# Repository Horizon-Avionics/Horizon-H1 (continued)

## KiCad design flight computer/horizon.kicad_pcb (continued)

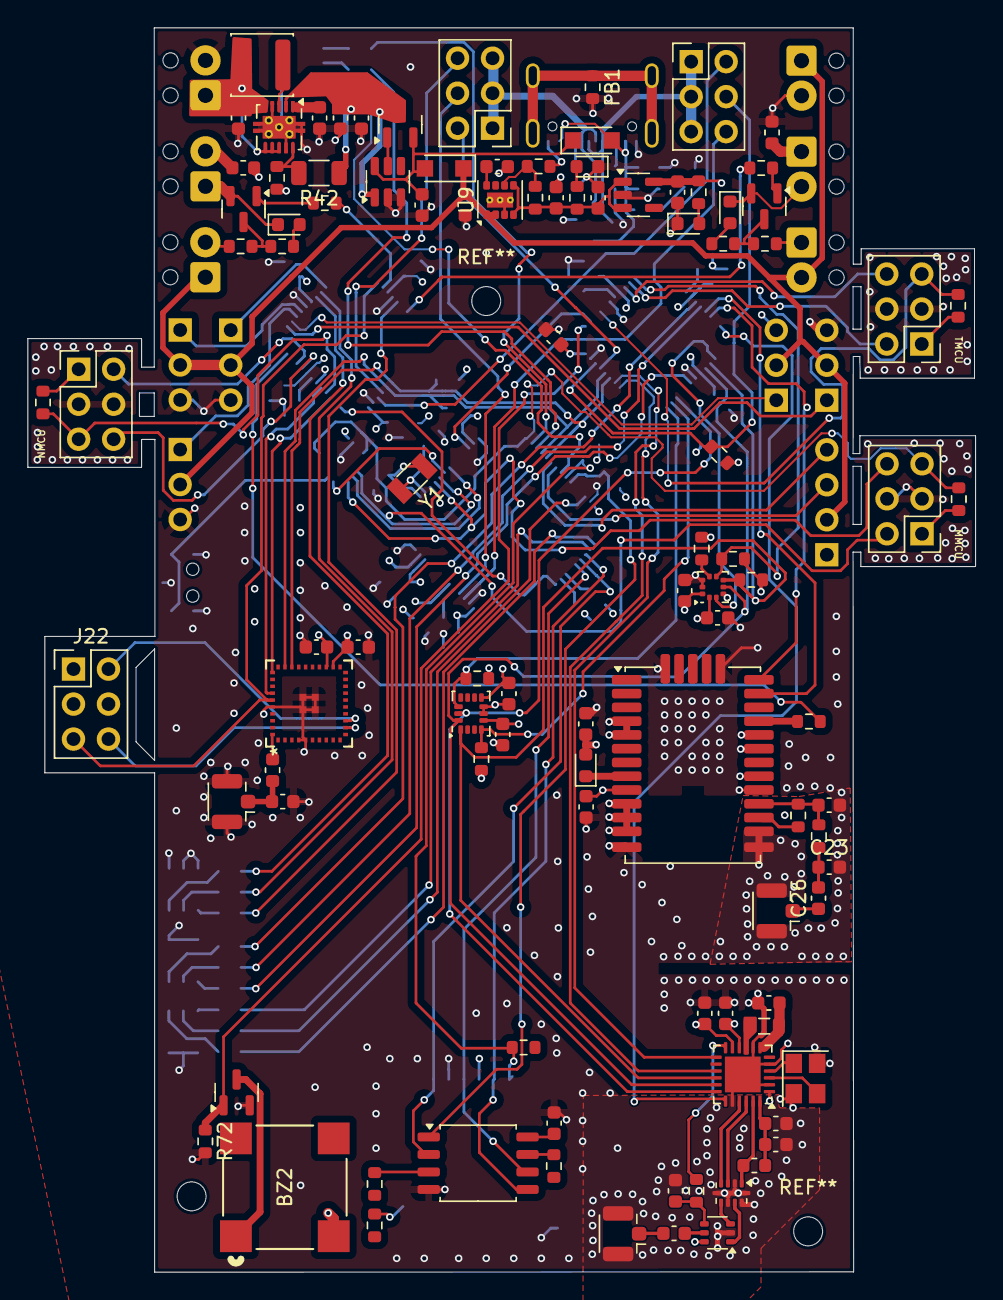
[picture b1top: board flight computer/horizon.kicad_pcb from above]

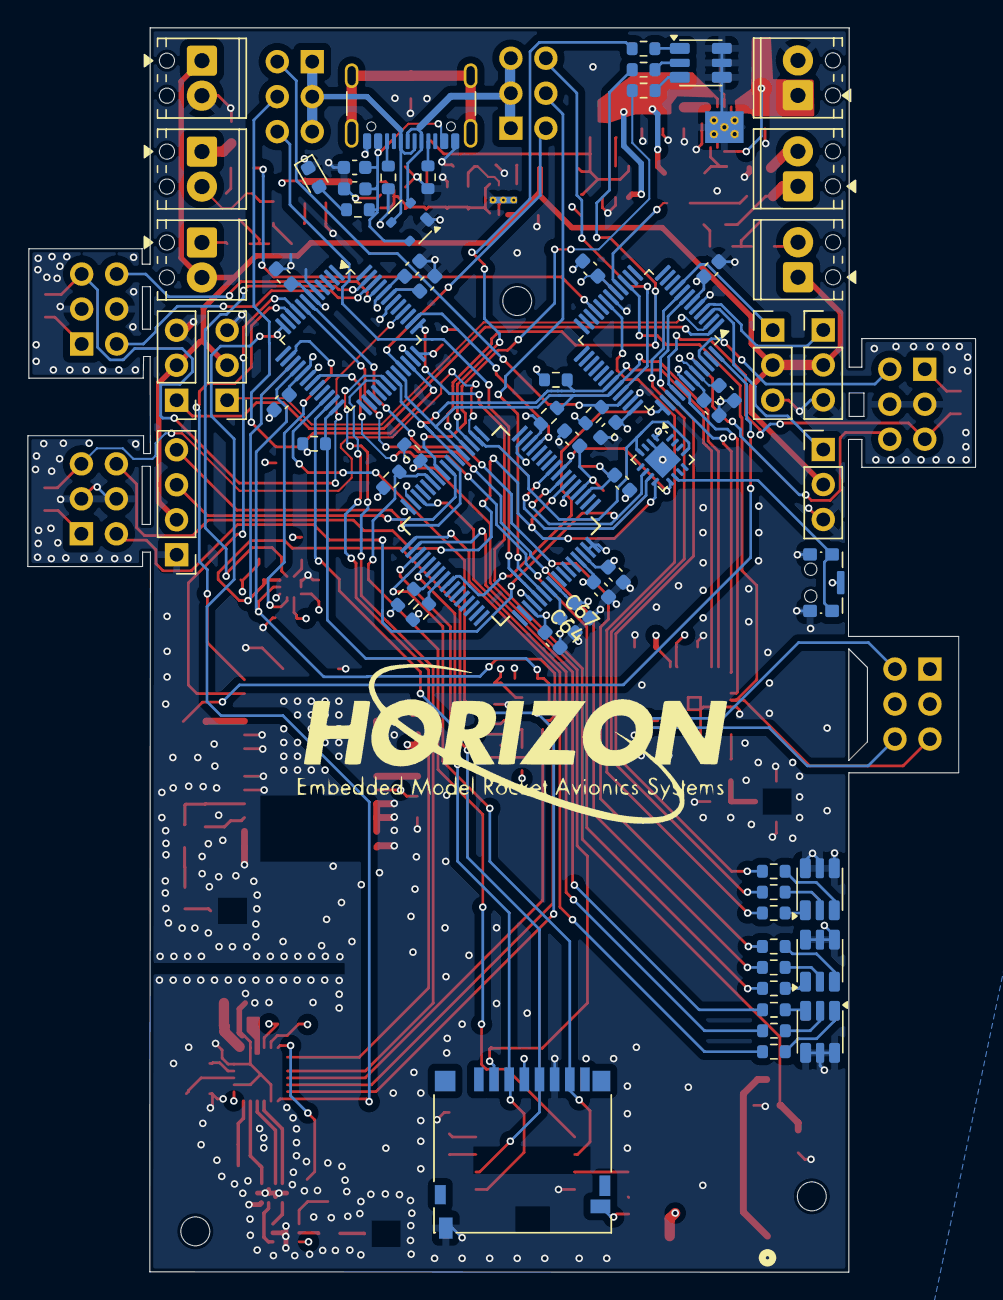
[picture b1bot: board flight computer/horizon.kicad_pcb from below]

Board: 4 copper layers, 68.8 x 90.3 mm, 169 parts (66 on the bottom side), 147 nets.

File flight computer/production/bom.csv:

Designator,Footprint,Quantity,Value,LCSC Part #
1X3SERVO1,PinHeader_1x03_P2.54mm_Vertical,1,Conn_01x03,
BZ2,MLT-8530_JHE,1,Buzzer,
"C1, C2",0603,2,100 nF,
"C10, C17",0603,2,12pF,
"C11, C13, C15, C19, C44, C45, C5, C50, C51, C6, C7, C77, C8, C9",0603,14,100nF,
"C12, C22, C35, C63, C72",0603,5,1uF,
C16,0603,1,4n7,
"C18, C67",0603,2,4.7uF,
"C20, C23, R1",0603,3,DNP,
"C21, C24, C25, C28, C32",0603,5,10uF,
C26,0603,1,100pF,
C27,0603,1,100n,
C33,0603,1,3.3 nF,
C34,0603,1,22uF,
C36,0603,1,1u,
"C37, C38",0603,2,100nF,C14663
C4,0603,1,1.2 pF,
C40,0603,1,470nF,C1623
C46,0603,1,1nF,C100040
C47,0603,1,47nF,C107093
C48,0603,1,47pF,C105622
C49,0603,1,100pF,C14665
"C64, C65, C66",0603,3,0.1uF,
D1,0603,1,D_Schottky,
"D15, D16, D17, D18",LED_ROHM_SMLVN6,4,SMLVN6RGB,
"D20, D26",Nexperia_CFP3_SOD-123W,2,PMEG6020ER,
"D21, D22, D3, D4, D7",0603,5,LED,
D8,SOT-143,1,PRTR5V0U2X,
"F1, F2",0603,2,Polyfuse,
FB1,0603,1,BLM18AG601SN1D,
J1,microSD_HC_Hirose_DM3D-SF,1,Micro_SD_Card_Det1,
J10,"TerminalBlock_Phoenix_MPT-0,5-2-2.54_1x02_P2.54mm_Horizontal",1,Conn_01x02_Pin,
J11,USB_C_Receptacle_GCT_USB4105-xx-A_16P_TopMnt_Horizontal,1,USB_C_Receptacle_USB2.0_16P,
J12,PinHeader_1x04_P2.54mm_Vertical,1,Conn_01x04,
"J13, J14, J6, J9",PinHeader_1x03_P2.54mm_Vertical,4,1x3 servo,
"J15, J16","TerminalBlock_Phoenix_MPT-0,5-2-2.54_1x02_P2.54mm_Horizontal",2,arming terminal,
"J17, J3, J4",U.FL_Hirose_U.FL-R-SMT-1_Vertical,3,H9161TR-ND,
"J18, J2, J21, J7, J8",PinHeader_2x03_P2.54mm_Vertical,5,Conn_02x03_Counter_Clockwise,
"J19, J20","TerminalBlock_Phoenix_MPT-0,5-2-2.54_1x02_P2.54mm_Horizontal",2,Screw_Terminal_01x02,
J22,PinHeader_2x03_P2.54mm_Vertical,1,Bluetooth Programming,
J5,"TerminalBlock_Phoenix_MPT-0,5-2-2.54_1x02_P2.54mm_Horizontal",1,Screw_Term,
L10,0603,1,47nH,C285885
L11,0805,1,15uH,C383402
L2,L_APV_ANR4018,1,2.2uH,
L3,0603,1,3.9 nH,
Q2,SOT-23,1,DMG2301L,
Q7,SOT-23,1,BSS138,
"Q8, Q9",SOT-23,2,IRLML6402,
"R10, R13, R26, R29, R30",0603,5,2.2k,
"R11, R12, R54, R55",0603,4,10kΩ,
"R14, R9",0603,2,1.5k,
R2,0603,1,0R,
"R20, R21",0603,2,5k1,
"R22, R47",0603,2,330,
"R27, R3, R38, R39, R4, R5, R52, R53, R56, R78, R80",0603,11,10k,
R42,1206,1,900k,
"R43, R45",0603,2,100k,
R44,0603,1,350k,
"R46, R79, R81",0603,3,100,
"R58, R59",0603,2,1k,
"R6, R7",0603,2,4.7k,
R72,0603,1,2k2,
R8,0603,1,100,C105588
"R87, R88, R89, R90, R91, R92, R93, R94, R95, R96, R97, R98",0603,12,220,
SAMD21G18A-AU1,TQFP-48_7x7mm_P0.5mm,1,NMCU,
SAMD21G18A-AU2,TQFP-48_7x7mm_P0.5mm,1,TMCU,
SW1,SW_SPST_CK_KMS2xxGP,1,CK_KMS2xxG,
U1,QFP50P1200X1200X160-64N,1,MMCU,
U10,LGA-14_3x2.5mm_P0.5mm_LayoutBorder3x4y,1,LSM6DS3,
U11,BGM220S_SIL,1,BGM220SC12WGA2R,
U13,TSOT-23-6,1,LTC4412xS6,
U15,SOT-23-5,1,AP2112K-3.3,
U16,QFN-24-1EP_4x4mm_P0.5mm_EP2.6x2.6mm,1,SX1262IMLTRT,C191341
U17,SOT-363_SC-70-6,1,PE4259, C470892
U2,QFN-16-1EP_3x3mm_P0.5mm_EP1.9x1.9mm,1,MKL02Z32VFG4,
U3,Texas_S-PVSON-N10_ThermalVias,1,TPS61200DRC,
U5,ST_HLGA-10_2x2mm_P0.5mm_LayoutBorder3x2y,1,LPS22HB,
U6,Quectel_L96,1,GPS,
U8,SOIC-8_5.3x5.3mm_P1.27mm,1,NAND,
U9,Texas_SIL0008D_MicroSiP-8-1EP_2.8x3mm_P0.65mm_EP1.1x1.9mm_ThermalVias,1,TPS82130,
Y1,Crystal_SMD_3215-2Pin_3.2x1.5mm,1,32 kHZ,
Y2,Crystal_SMD_3225-4Pin_3.2x2.5mm,1,32MHz,C37635386

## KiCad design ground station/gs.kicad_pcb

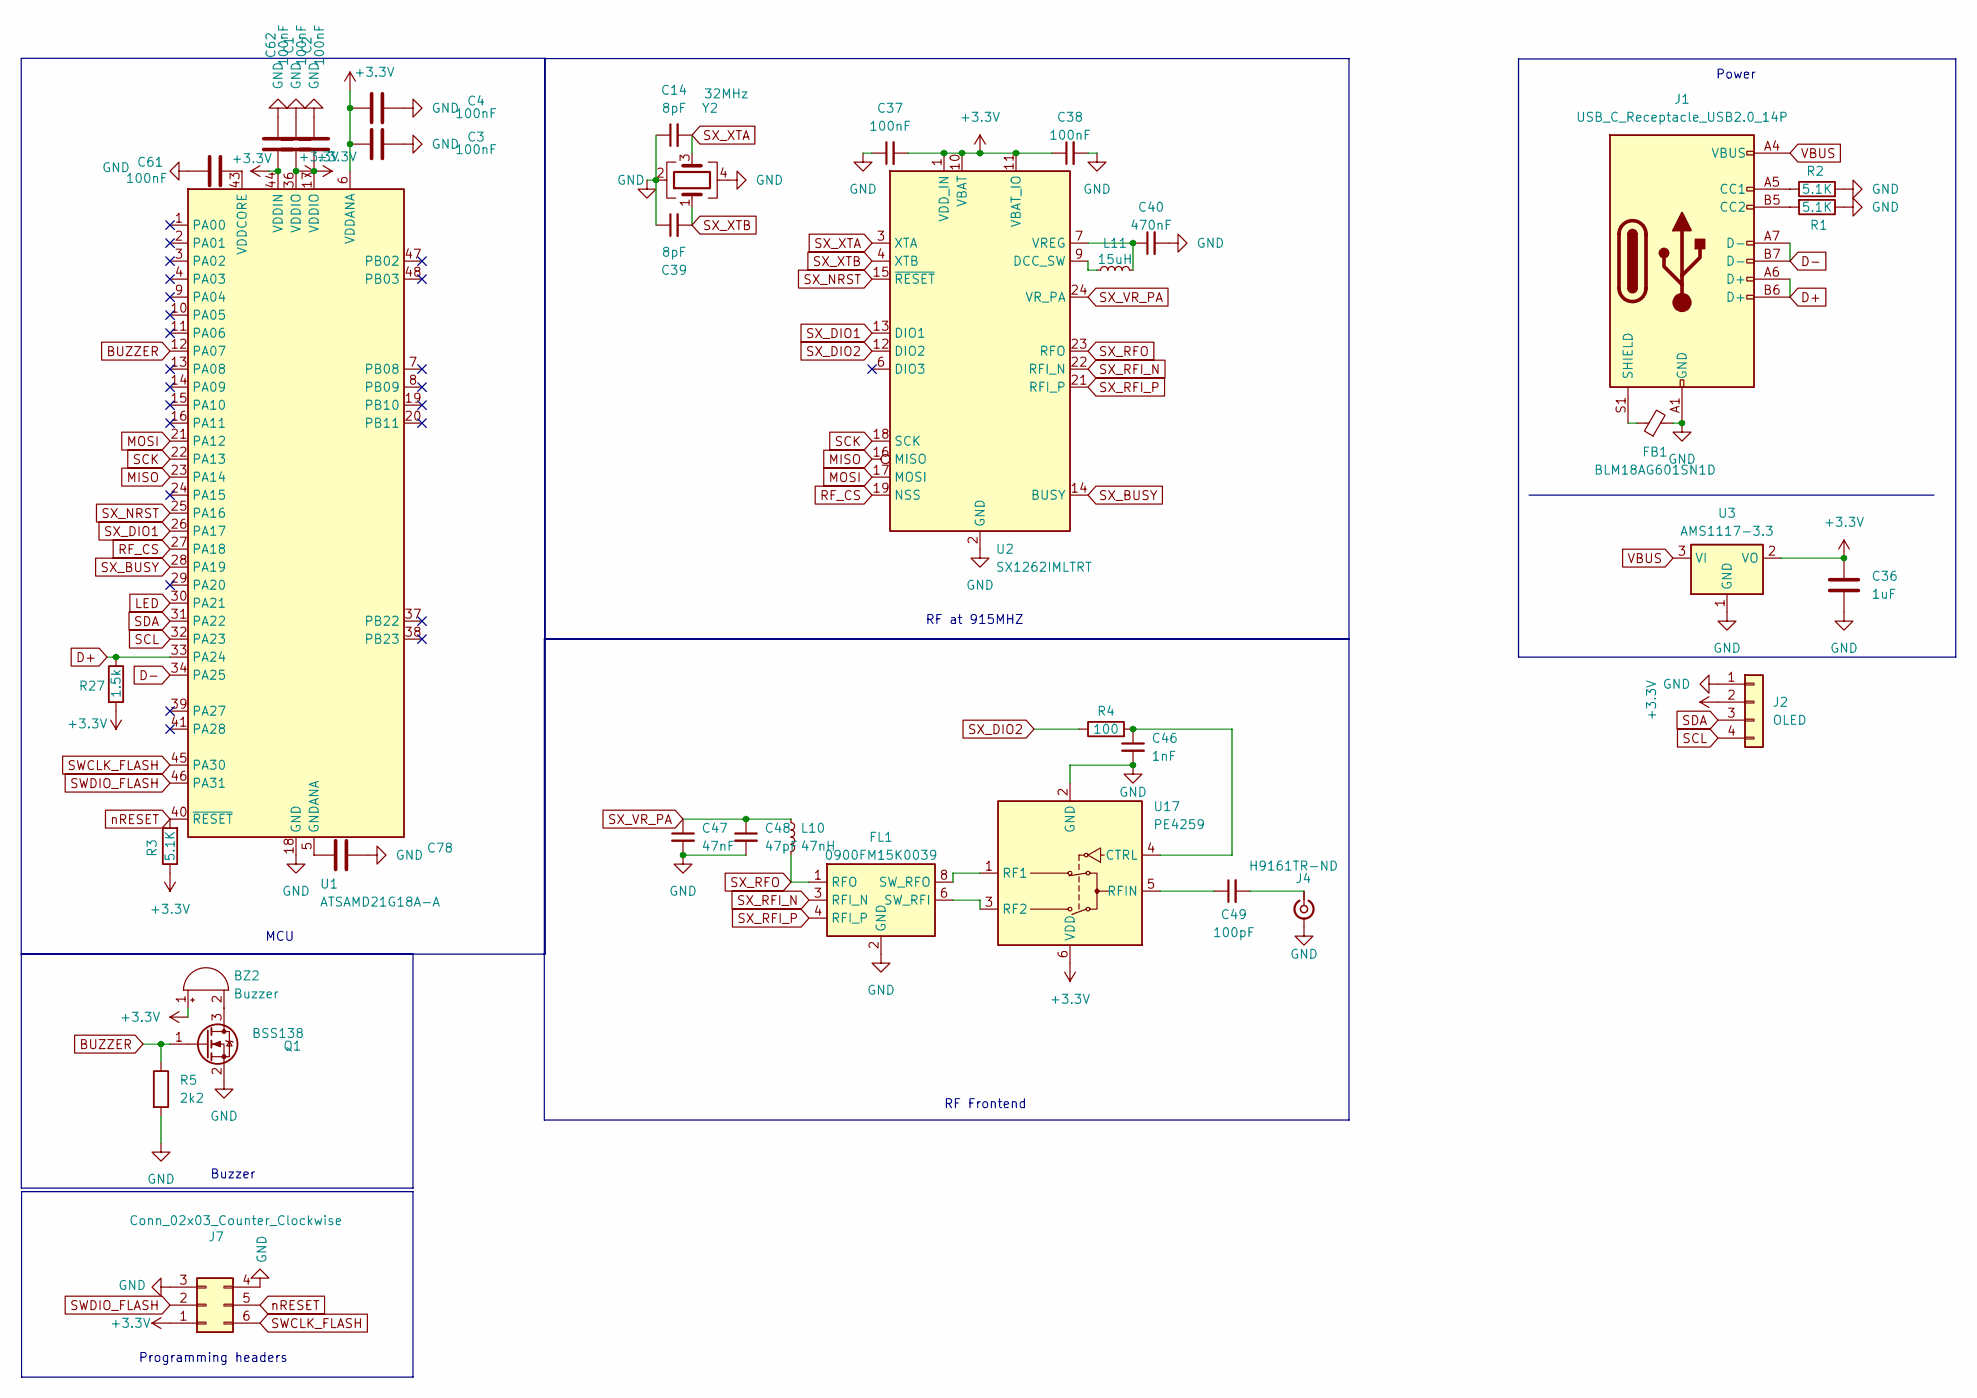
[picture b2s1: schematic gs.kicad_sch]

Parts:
BZ2: Buzzer; MagneticBuzzer_PUI_AT-0927-TT-6-R
C1, C2, C3, C4, C61, C62, C78: 100nF; C_0603_1608Metric
C14, C39: 8pF; C_0603_1608Metric; LCSC Part C327316
C36: 1uF; C_0603_1608Metric
C37, C38: 100nF; C_0603_1608Metric; LCSC Part C14663
C40: 470nF; C_0603_1608Metric; LCSC Part C1623
C46: 1nF; C_0603_1608Metric; LCSC Part C100040
C47: 47nF; C_0603_1608Metric; LCSC Part C107093
C48: 47pF; C_0603_1608Metric; LCSC Part C105622
C49: 100pF; C_0603_1608Metric; LCSC Part C14665
FB1: BLM18AG601SN1D; R_0603_1608Metric; LCSC Part C19330
FL1: 0900FM15K0039; Balun_Johanson_0900FM15K0039; LCSC Part C5224443
J1: USB_C_Receptacle_USB2.0_14P; USB_C_Receptacle_HCTL_HC-TYPE-C-16P-01A
J2: OLED; NS-Tech_Grove_1x04_P2mm_Vertical
J4: H9161TR-ND; U.FL_Hirose_U.FL-R-SMT-1_Vertical
J7: Conn_02x03_Counter_Clockwise; PinHeader_2x03_P2.54mm_Vertical
L10: 47nH; L_0603_1608Metric; LCSC Part C285885
L11: 15uH; L_0805_2012Metric; LCSC Part C383402
Q1: BSS138; SOT-23
R1, R2, R3: 5.1K; C_0603_1608Metric
R4: 100; R_0603_1608Metric
R5: 2k2; R_0603_1608Metric
R27: 1.5k; R_0603_1608Metric
U1: ATSAMD21G18A-A; TQFP-48_7x7mm_P0.5mm
U2: SX1262IMLTRT; QFN-24-1EP_4x4mm_P0.5mm_EP2.6x2.6mm
U3: AMS1117-3.3; SOT-223-3_TabPin2
U17: PE4259; SOT-363_SC-70-6; LCSC Part C470892
Y2: 32MHz; Crystal_SMD_3225-4Pin_3.2x2.5mm; LCSC Part C37635386

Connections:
+3.3V: BZ2.1 (+), C1.2, C2.2, C3.2, C4.2, C36.1, C37.2, C38.1, C62.2, J2.2, J7.1, R3.1, R27.2, U1.6 (VDDANA), U1.17 (VDDIO), U1.36 (VDDIO), U1.44 (VDDIN), U2.1 (VDD_IN), U2.10 (VBAT), U2.11 (VBAT_IO), U3.2 (VO), U17.6 (VDD)
BUZZER: Q1.1 (G), R5.1, U1.12 (PA07)
D+: J1.A6 (D+), J1.B6 (D+), R27.1, U1.33 (PA24)
D-: J1.A7 (D-), J1.B7 (D-), U1.34 (PA25)
GND: C1.1, C2.1, C3.1, C4.1, C14.1, C36.2, C37.1, C38.2, C39.1, C40.2, C46.2, C47.2, C48.2, C61.1, C62.1, C78.1, FB1.2, FL1.2 (GND), FL1.5 (GND), FL1.7 (GND), FL1.9 (GND), FL1.10 (GND), J1.A1 (GND), J1.A12 (GND), J1.B1 (GND), J1.B12 (GND), J2.1, J4.2 (Ext), J7.3, J7.4, Q1.2 (S), R1.1, R2.2, R5.2, U1.18 (GND), U1.35 (GND), U1.42 (GND), U2.2 (GND), U2.5 (GND), U2.8 (GND), U2.20 (GND), U2.25 (GND), U3.1 (GND), U17.2 (GND), Y2.2, Y2.4
LED: U1.30 (PA21)
MISO: U1.23 (PA14), U2.16 (MISO)
MOSI: U1.21 (PA12), U2.17 (MOSI)
unnamed: BZ2.2 (-), Q1.3 (D)
unnamed: FL1.6 (SW_RFI), U17.3 (RF2)
unnamed: FL1.8 (SW_RFO), U17.1 (RF1)
unnamed: J1.A5 (CC1), R2.1
unnamed: J1.B5 (CC2), R1.2
unnamed: FB1.1, J1.S1 (SHIELD)
unnamed: C49.2, J4.1 (In)
unnamed: C78.2, U1.5 (GNDANA)
unnamed: C61.2, U1.43 (VDDCORE)
unnamed: L11.1, U2.9 (DCC_SW)
unnamed: C40.1, L11.2, U2.7 (VREG)
unnamed: C46.1, R4.2, U17.4 (CTRL)
unnamed: C49.1, U17.5 (RFIN)
RF_CS: U1.27 (PA18), U2.19 (NSS)
SCK: U1.22 (PA13), U2.18 (SCK)
SCL: J2.4, U1.32 (PA23)
SDA: J2.3, U1.31 (PA22)
SWCLK_FLASH: J7.6, U1.45 (PA30)
SWDIO_FLASH: J7.2, U1.46 (PA31)
SX_BUSY: U1.28 (PA19), U2.14 (BUSY)
SX_DIO1: U1.26 (PA17), U2.13 (DIO1)
SX_DIO2: R4.1, U2.12 (DIO2)
SX_NRST: U1.25 (PA16), U2.15 (~RESET)
SX_RFI_N: FL1.3 (RFI_N), U2.22 (RFI_N)
SX_RFI_P: FL1.4 (RFI_P), U2.21 (RFI_P)
SX_RFO: FL1.1 (RFO), L10.2, U2.23 (RFO)
SX_VR_PA: C47.1, C48.1, L10.1, U2.24 (VR_PA)
SX_XTA: C14.2, U2.3 (XTA), Y2.3
SX_XTB: C39.2, U2.4 (XTB), Y2.1
VBUS: J1.A4 (VBUS), J1.A9 (VBUS), J1.B4 (VBUS), J1.B9 (VBUS), U3.3 (VI)
nRESET: J7.5, R3.2, U1.40 (~RESET)

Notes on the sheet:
Programming headers
Buzzer
RF at 915MHZ
RF Frontend
Power
MCU

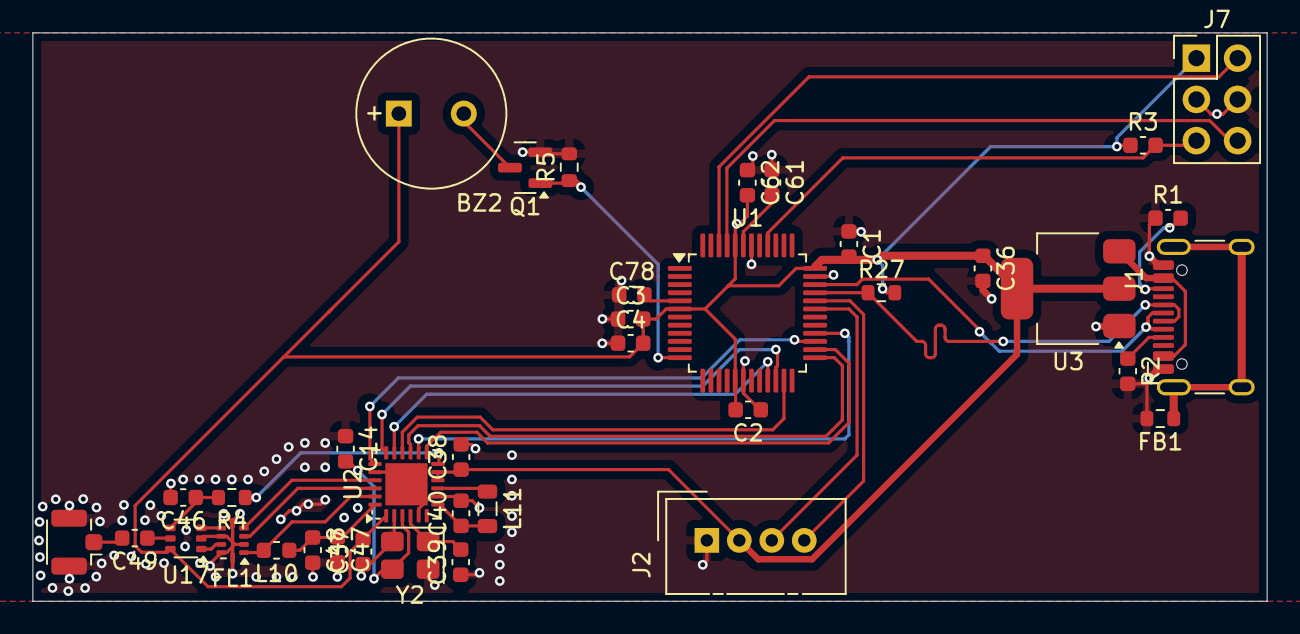
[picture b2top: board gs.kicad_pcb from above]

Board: 2 copper layers, 76.0 x 35.0 mm, 38 parts (0 on the bottom side), 38 nets.

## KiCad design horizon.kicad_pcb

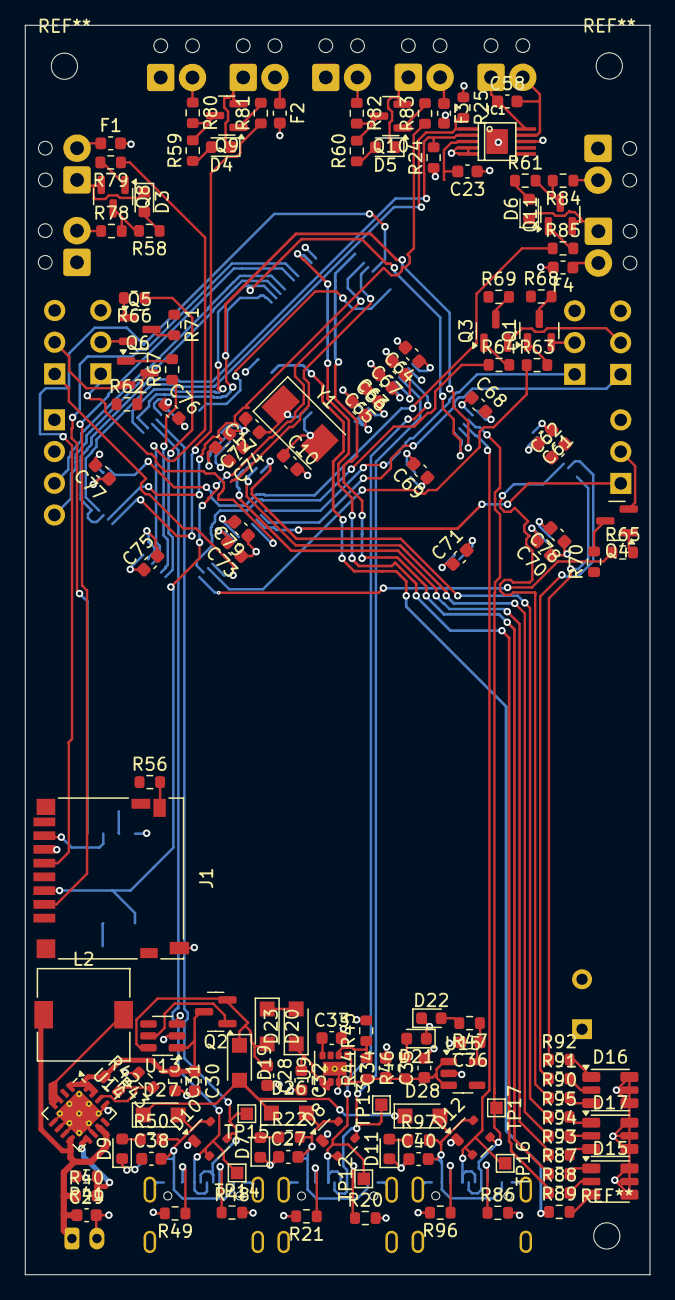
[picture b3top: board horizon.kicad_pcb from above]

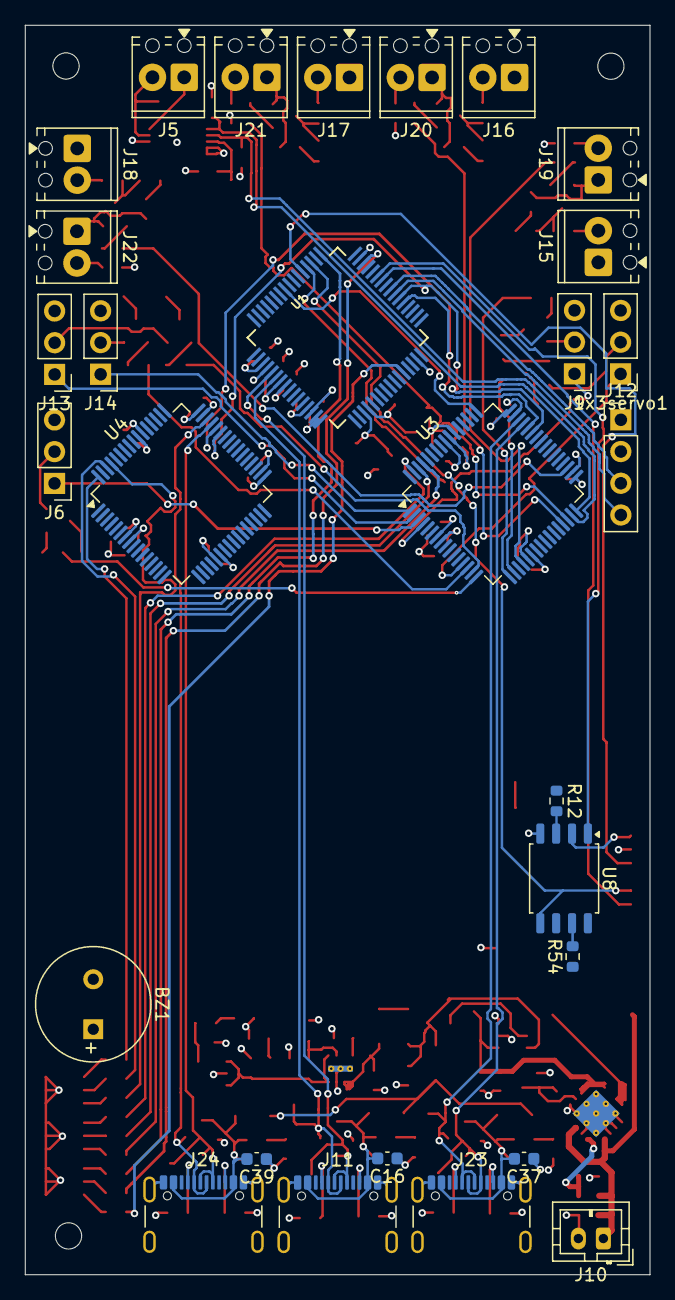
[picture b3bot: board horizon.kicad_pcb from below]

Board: 4 copper layers, 50.0 x 100.0 mm, 164 parts (29 on the bottom side), 131 nets.

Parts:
1x3servo1: Conn_01x03; PinHeader_1x03_P2.54mm_Vertical
BZ1: Buzzer; MagneticBuzzer_PUI_AT-0927-TT-6-R
C10, C17: 12pF; C_0603_1608Metric
C16, C37, C39: 4n7; C_0603_1608Metric
C23: 100 nF; C_0603_1608Metric
C27, C38, C40: 100n; C_0603_1608Metric
C28, C32: 10uF; C_0603_1608Metric
C29: 10u; C_0603_1608Metric
C30: 2u2; C_0603_1608Metric
C31: 100u; C_0603_1608Metric
C33: 3.3 nF; C_0603_1608Metric
C34: 22uF; C_0603_1608Metric
C35, C63, C72: 1uF; C_0603_1608Metric
C36: 1u; C_0603_1608Metric
C58, C61, C62, C68, C69, C70, C71, C73, C74, C75, C76, C77, C78, C79: 100nF; C_0603_1608Metric
C64, C65, C66: 0.1uF; C_0603_1608Metric
C67: 4.7uF; C_0603_1608Metric
D3, D4, D5, D6, D7, D9, D11, D21, D22: LED; LED_0603_1608Metric
D8, D10, D12: PRTR5V0U2X; SOT-143
D15, D16, D17: SMLVN6RGB; LED_ROHM_SMLVN6
D19, D20, D23, D26, D27, D28: PMEG6020ER; Nexperia_CFP3_SOD-123W
F1, F2, F3, F4: Polyfuse; Fuse_0603_1608Metric
IC1: A3909; MSOP10-PAD
J1: Micro_SD_Card_Det1; microSD_HC_Hirose_DM3D-SF
J5: Screw_Term; TerminalBlock_Phoenix_MPT-0,5-2-2.54_1x02_P2.54mm_Horizontal
J6, J9, J13, J14: 1x3 servo; PinHeader_1x03_P2.54mm_Vertical
J10: Conn_01x02_Pin; JST_PH_B2B-PH-K_1x02_P2.00mm_Vertical
J11, J23, J24: USB_C_Receptacle_USB2.0_16P; USB_C_Receptacle_GCT_USB4105-xx-A_16P_TopMnt_Horizontal
J12: Conn_01x04; PinHeader_1x04_P2.54mm_Vertical
J15, J16, J17, J18: arming terminal; TerminalBlock_Phoenix_MPT-0,5-2-2.54_1x02_P2.54mm_Horizontal
J19, J20, J21, J22: Screw_Terminal_01x02; TerminalBlock_Phoenix_MPT-0,5-2-2.54_1x02_P2.54mm_Horizontal
L2: SLF7055T-6R8N2R8-3PF; L_7.3x7.3_H4.5
Q1, Q3, Q4, Q5, Q6, Q8, Q9, Q10, Q11: IRLML6402; SOT-23
Q2: DMG2301L; SOT-23
R12, R54: 10kΩ; R_0603_1608Metric
R20, R21, R48, R49, R86, R96: 5k1; R_0603_1608Metric
R22, R47, R50, R97: 330; R_0603_1608Metric
R24, R25, R56, R78, R80, R82, R84: 10k; R_0603_1608Metric
R40, R41, R43, R45, R62, R68, R69, R70, R71: 100k; R_0603_1608Metric
R42: 430k; R_0603_1608Metric
R44: 350k; R_0603_1608Metric
R46, R63, R64, R65, R66, R67, R79, R81, R83, R85: 100; R_0603_1608Metric
R58, R59, R60, R61: 1k; R_0603_1608Metric
R87, R88, R89, R90, R91, R92, R93, R94, R95: 220; R_0603_1608Metric
TP12, TP13, TP14, TP15, TP16, TP17: TestPoint; TestPoint_Pad_1.0x1.0mm
U1: MMCU; QFP50P1200X1200X160-64N
U3: NMCU; TQFP-64_10x10mm_P0.5mm
U4: TMCU; TQFP-64_10x10mm_P0.5mm
U8: NAND; SOIC-8_5.3x5.3mm_P1.27mm
U9: TPS82130; Texas_SIL0008D_MicroSiP-8-1EP_2.8x3mm_P0.65mm_EP1.1x1.9mm_T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
U13: LTC4412xS6; TSOT-23-6
U14: TPS61092; Texas_RSA_VQFN-16-1EP_4x4mm_P0.65mm_EP2.7x2.7mm_ThermalVias
U15: AP2112K-3.3; SOT-23-5
Y1: Crystal; Crystal_SMD_0603-2Pin_6.0x3.5mm

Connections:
1B: R87.1, U1.49 (D10/TX2/PWM)
1G: R88.1, U1.46 (D9/RX2/PWM)
1R: R89.1, U1.28 (D3/CAN-TX/PWM)
2B: R92.1, U4.64 (PB03)
2G: R91.1, U4.62 (PB01)
2R: R90.1, U4.61 (PB00)
3B: R95.1, U3.63 (PB02)
3G: R94.1, U3.62 (PB01)
3R: R93.1, U3.61 (PB00)
+3.3V: BZ1.1 (+), C36.1, C62.2, C63.1, C64.1, C65.1, C66.1, C68.2, C69.2, C70.2, C71.2, C73.2, C74.2, C75.2, C76.2, C77.2, J1.4 (VDD), R12.1, R47.1, R54.1, R56.1, U1.3 (VCC), U1.8 (VREGIN), U1.13 (VCCA), U1.14 (VREF-H), U1.21 (VBAT), U1.30 (VCC), U1.48 (VCC), U3.8 (VDDANA), U3.21 (VDDIO), U3.34 (VDDIO), U3.48 (VDDIO), U3.56 (VDDIN), U4.8 (VDDANA), U4.21 (VDDIO), U4.34 (VDDIO), U4.48 (VDDIO), U4.56 (VDDIN), U8.8 (VCC), U15.5 (VOUT)
+5V: C23.2, D20.1 (K), D23.2 (A), IC1.3 (VBB), J12.2, J15.1, J16.1, J17.1, J18.1, R62.1, R68.1, R69.1, R70.1, R71.1
CAM_RX: J12.3, U1.40 (D1/TX1/TOUCH)
CAM_TX: J12.4, U1.39 (D0/RX1/TOUCH)
CS_NAND MMCU: U1.43 (D15/A1/TOUCH), U8.1 (~CS)
CS_SD MMCU: J1.2 (DAT3/CD), U1.42 (D25/PWM/TOUCH)
D+ DMCU-1: D10.2 (I/O1), J23.A6 (D+), J23.B6 (D+), TP14.1, U3.45 (PA24)
D+ DMCU-2: D12.2 (I/O1), J24.A6 (D+), J24.B6 (D+), TP16.1, U4.45 (PA24)
D+ MMCU: D8.2 (I/O1), J11.A6 (D+), J11.B6 (D+), TP12.1, U1.5 (USB-P)
D- DMCU-1: D10.3 (I/O2), J23.A7 (D-), J23.B7 (D-), TP15.1, U3.46 (PA25)
D- DMCU-2: D12.3 (I/O2), J24.A7 (D-), J24.B7 (D-), TP17.1, U4.46 (PA25)
D- MMCU: D8.3 (I/O2), J11.A7 (D-), J11.B7 (D-), TP13.1, U1.6 (USB-M)
DIR1: IC1.2 (IN2), R24.2, U3.31 (PA14)
GND: 1x3servo1.3, C10.2, C16.1, C17.2, C23.1, C27.1, C28.2, C29.2, C30.2, C31.2, C32.2, C33.2, C34.2, C35.2, C36.2, C37.1, C38.1, C39.1, C40.1, C61.1, C62.1, C63.2, C64.2, C65.2, C66.2, C67.2, C68.1, C69.1, C70.1, C71.1, C72.1, C73.1, C74.1, C75.1, C76.1, C77.1, C78.1, C79.1, D7.1 (K), D8.1 (GND), D9.1 (K), D10.1 (GND), D11.1 (K), D12.1 (GND), D15.4 (GK), D15.5 (RK), D15.6 (BK), D16.4 (GK), D16.5 (RK), D16.6 (BK), D17.4 (GK), D17.5 (RK), D17.6 (BK), D21.1 (K), D22.1 (K), F1.2, F2.2, F3.2, F4.2, IC1.4 (IN3), IC1.5 (IN4), IC1.8 (GND), IC1.TP (GND), J1.6 (VSS), J1.10 (SHIELD), J6.3, J9.3, J10.2, J11.A1 (GND), J11.A12 (GND), J11.B1 (GND), J11.B12 (GND), J11.S1 (SHIELD), J12.1, J13.3, J14.3, J23.A1 (GND), J23.A12 (GND), J23.B1 (GND), J23.B12 (GND), J23.S1 (SHIELD), J24.A1 (GND), J24.A12 (GND), J24.B1 (GND), J24.B12 (GND), J24.S1 (SHIELD), R20.2, R21.2, R24.1, R25.1, R41.2, R43.2, R45.2, R48.2, R49.2, R86.2, R96.2, U1.4 (VSS), U1.15 (VREF-L), U1.16 (VSSA), U1.31 (VSS), U1.47 (VSS), U3.22 (GND), U3.33 (GND), U3.47 (GND), U3.54 (GND), U4.22 (GND), U4.33 (GND), U4.47 (GND), U4.54 (GND), U8.4 (GND), U9.3 (GND), U9.9 (GND), U13.2 (GND), U13.3 (CTL), U14.5 (PGND), U14.6 (PGND), U14.7 (PGND), U14.10 (SYNC), U14.13 (GND), U14.17 (PAD), U15.2 (GND)
I2C0_SCL: U1.37 (D19/A5/SCL0/TOUCH), U3.44 (PA23), U4.44 (PA23)
I2C0_SDA: U1.38 (D18/A4/SDA0/TOUCH), U3.43 (PA22), U4.43 (PA22)
NAND_MISO MMCU: J1.7 (DAT0), U1.52 (D12/MISO), U8.2 (DO/IO_{1})
NAND_MOSI MMCU: J1.3 (CMD), U1.51 (D11/MOSI), U8.5 (DI/IO_{0})
unnamed: 1x3servo1.2, Q6.2 (S)
unnamed: D3.2 (A), R58.1
unnamed: D3.1 (K), J19.1, Q8.2 (S)
unnamed: D4.2 (A), R59.1
unnamed: D4.1 (K), J20.1, Q9.2 (S)
unnamed: D5.2 (A), R60.1
unnamed: D5.1 (K), J21.1, Q10.2 (S)
unnamed: D6.2 (A), R61.1
unnamed: D6.1 (K), J22.1, Q11.2 (S)
unnamed: D7.2 (A), R22.1
unnamed: D9.2 (A), R50.1
unnamed: C37.2, C38.2, D10.4 (VCC), D27.2 (A), J23.A4 (VBUS), J23.A9 (VBUS), J23.B4 (VBUS), J23.B9 (VBUS), R50.2
unnamed: D11.2 (A), R97.1
unnamed: C39.2, C40.2, D12.4 (VCC), D28.2 (A), J24.A4 (VBUS), J24.A9 (VBUS), J24.B4 (VBUS), J24.B9 (VBUS), R97.2
unnamed: D15.1 (BA), R87.2
unnamed: D15.3 (GA), R89.2
unnamed: D15.2 (RA), R88.2
unnamed: D16.1 (BA), R92.2
unnamed: D16.3 (GA), R90.2
unnamed: D16.2 (RA), R91.2
unnamed: D17.1 (BA), R95.2
unnamed: D17.3 (GA), R93.2
unnamed: D17.2 (RA), R94.2
unnamed: D21.2 (A), R46.2
unnamed: D22.2 (A), R47.2
unnamed: C32.1, D23.1 (K), U9.1 (EN), U9.2 (VIN)
unnamed: C16.2, C27.2, D8.4 (VCC), D26.2 (A), J11.A4 (VBUS), J11.A9 (VBUS), J11.B4 (VBUS), J11.B9 (VBUS), R22.2
unnamed: C58.1, IC1.10 (OUT1), J5.1
unnamed: C58.2, IC1.9 (OUT2), J5.2
unnamed: J6.2, Q4.2 (S)
unnamed: J9.2, Q5.2 (S)
unnamed: C29.1, J10.1, L2.1, R40.1, U14.8 (VBAT), U14.11 (EN)
unnamed: J11.A5 (CC1), R20.1
unnamed: J11.B5 (CC2), R21.1
unnamed: J13.2, Q3.2 (S)
unnamed: J14.2, Q1.2 (S)
unnamed: J15.2, R78.1
unnamed: J16.2, R80.1
unnamed: J17.2, R82.1
unnamed: J18.2, R84.1
unnamed: F1.1, J19.2
unnamed: F2.1, J20.2
unnamed: F3.1, J21.2
unnamed: F4.1, J22.2
unnamed: J23.A5 (CC1), R48.1
unnamed: J23.B5 (CC2), R49.1
unnamed: J24.A5 (CC1), R86.1
unnamed: J24.B5 (CC2), R96.1
unnamed: L2.2, U14.3 (SW), U14.4 (SW)
unnamed: Q1.3 (D), R68.2
unnamed: Q1.1 (G), R63.2
unnamed: Q2.1 (G), U13.5 (GATE)
unnamed: Q3.3 (D), R69.2
unnamed: Q3.1 (G), R64.2
unnamed: Q4.3 (D), R70.2
unnamed: Q4.1 (G), R65.2
unnamed: Q5.3 (D), R71.2
unnamed: Q5.1 (G), R66.2
unnamed: Q6.3 (D), R62.2
unnamed: Q6.1 (G), R67.2
unnamed: Q8.3 (D), R58.2, R78.2
unnamed: Q8.1 (G), R79.2
unnamed: Q9.3 (D), R59.2, R80.2
unnamed: Q9.1 (G), R81.2
unnamed: Q10.3 (D), R60.2, R82.2
unnamed: Q10.1 (G), R83.2
unnamed: Q11.3 (D), R61.2, R84.2
unnamed: Q11.1 (G), R85.2
unnamed: C17.1, U1.20 (EXTAL32), Y1.1
unnamed: C67.1, U1.7 (VOUT3V3)
unnamed: C10.1, U1.19 (XTAL32), Y1.2
unnamed: C79.2, U3.7 (GNDANA)
unnamed: C72.2, U3.55 (VDDCORE)
unnamed: C78.2, U4.7 (GNDANA)
unnamed: C61.2, U4.55 (VDDCORE)
unnamed: R54.2, U8.7 (~HOLD/~RESET/IO_{3})
unnamed: R12.2, U8.3 (~WP/IO_{2})
unnamed: R44.2, R45.1, U9.6 (FB)
unnamed: C33.1, U9.8 (SS/TR)
unnamed: R42.2, R43.1, U14.14 (FB)
unnamed: R40.2, R41.1, U14.9 (LBI)
unnamed: C34.1, C35.1, R44.1, R46.1, U9.4 (VOUT), U9.5 (VOUT), U15.1 (VIN), U15.3 (EN)
POWAAAA: C28.1, D19.1 (K), D20.2 (A), Q2.2 (S), U13.6 (SENSE)
PTA12: U1.29 (D4/CAN-RX/PWM), U4.50 (PB23)
PTD4: U1.57 (D2), U3.49 (PB22)
PWM1: IC1.1 (IN1), R25.2, U3.32 (PA15)
SD_DETECT: J1.9 (DET), R56.2
SERVO1: J14.1, U3.1 (PA00)
SERVO2: J13.1, U3.2 (PA01)
SERVO3: J6.1, U3.3 (PA02)
SERVO4: J9.1, U3.4 (PA03)
SERVO5: 1x3servo1.1, U3.13 (PA04)
SPI0_SCK MMCU: J1.5 (CLK), U1.53 (D28/A17)
VBUS: D19.2 (A), D26.1 (K), D27.1 (K), D28.1 (K)
bat: C30.1, C31.1, Q2.3 (D), R42.1, U13.1 (VIN), U14.1 (VOUT), U14.15 (VOUT), U14.16 (VOUT)
mosfet1_signal: R63.1, U3.14 (PA05)
mosfet1_signalfire: R79.1, U3.20 (PA11)
mosfet2_signal: R64.1, U3.15 (PA06)
mosfet2_signalfire: R81.1, U3.29 (PA12)
mosfet3_signal: R65.1, U3.16 (PA07)
mosfet3_signalfire: R83.1, U3.30 (PA13)
mosfet4_signal: R66.1, U3.17 (PA08)
mosfet4_signalfire: R85.1, U3.35 (PA16)
mosfet5_signal: R67.1, U3.18 (PA09)

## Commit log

2025-05-09 Backlink to CADLAB.io has been added.
2025-05-11 test cardlab
2025-05-11 added all chips
2025-05-11 Added a start to the README and renamed some parts in KiCad
2025-05-11 More Writing yay
2025-05-11 input usb and random references
2025-05-12 idk what I changed
2025-05-13 usbc changes + voltage reg
2025-05-13 input regulation
2025-05-14 changes to power regulation
2025-05-14 data lines
2025-05-14 Header pins changes
2025-05-14 Finished with the headers
2025-05-14 data + bootloader pins
2025-05-14 switch for programming, data lines
2025-05-14 Added IMU Schematics and connected it to TMU via SPI
2025-05-14 Added like 1/3 of the GPS Schematic
2025-05-14 Baro schematics done
2025-05-14 SD Card is Done
2025-05-14 Some text additions
2025-05-14 INTCOMM Completed
2025-05-14 Labels
2025-05-14 set up hierarchy
2025-05-15 Changes, idr what though :(
2025-05-15 Add the Journal
2025-05-15 misc fixes
2025-05-15 GPS is done! yay
2025-05-15 RF at 915MHZ done!
2025-05-15 H-Bridge is done!
2025-05-15 Flag Changes- Important
2025-05-16 chip wiring fix
2025-05-16 servo mosfet, pyro mosfet, camera
2025-05-16 pin header rename
2025-05-16 MISC
2025-05-16 ERC Changes
2025-05-16 fixed wiring stuff and accessories
2025-05-16 footprints
2025-05-16 Movement changes for PCB
2025-05-16 clean up
2025-05-16 Trying to add GPS footprint
2025-05-16 Added GPS footprint
2025-05-16 i fogro
2025-05-17 schematic(not much)
2025-05-18 started pcb
2025-05-18 Hopefully added BL, and all the remaining footprints
2025-05-18 Added most of the 3d models
2025-05-18 pcb parts all wired
2025-05-18 Merged Fix of Schematic and PCB
2025-05-18 Added fill
2025-05-18 CS, and SCK for RF
2025-05-18 Started routing for BL
2025-05-18 do some rf routing (and hopefully not break everything)
2025-05-18 pcb layout done
2025-05-19 new usb, move micro sd, redo boost converter (pls find a place on the pcb tomorrow)
2025-05-19 production files
2025-05-20 flipped sides, changed footprint
2025-05-24 kinda redid layout
2025-05-24 finished layout
2025-05-24 wiring
2025-05-25 redoing wiring
2025-05-26 wiring i hate this
2025-05-27 more wiring
2025-05-27 files rearranged
2025-05-27 Added it back...
2025-06-01 Huge amount of PCB changes
2025-06-01 Wired up the IMU's to the MCU
2025-06-01 Ummm, more baro routing to the MCU and stuff
2025-06-01 MOSI routed
2025-06-01 Fixed the TBD's parts
2025-06-02 tspmo
2025-06-02 save spot not done dont push
2025-06-02 wiring almost done
2025-06-03 wiring + layout done
    wiring and layout done
    a lottt of stuff needs their 3v connected or 5v
2025-06-03 prlly wiring
2025-06-04 for you scooter <3
2025-06-04 Actually fixed too much broken stuff
2025-06-04 We Getting there... 84 errors left
2025-06-04 Bad DRC should be done
2025-06-04 Changes so meddy can work on it now ;)
2025-06-05 bootloader wiring. scooter can u pls finish
2025-06-05 Finish bootloader routing
2025-06-05 I def fixed a lot... not sure what though lol
2025-06-05 Highway Roadtrip point!
2025-06-05 drc fixes
2025-06-05 finished drc
2025-06-06 finished most of drc
2025-06-06 fixed stuffs
2025-06-06 Fixing some DRC
2025-06-06 Fixes some more
2025-06-06 More and more fixes
2025-06-09 scooter <3 liam
2025-06-09 drc not done
2025-06-13 Fixed All the DRC errors I'm pretty sure
2025-06-13 Some random tiding up
2025-06-15 idk, changes
2025-06-15 Forgot step file..
2025-06-15 Major ground pour fix and via stitching
2025-06-15 Switched Bl and GPS to U.FL connectors
2025-06-18 added logos
2025-06-18 added looks only file
2025-06-18 logo placement stuff
2025-06-22 Git Breaks
2025-06-22 Git breaking
2025-06-24 Finished the JOURNAL
2025-06-24 started to change to bridging and PCB stiching and stuff fixes
2025-06-25 Wired the headers for programming 3 MCU'S + some footprint fixes and additions for photos:(
2025-07-01 Added CAD
2025-07-02 Started wiring the teensy bootloader
2025-07-02 Finished wiring the teensy bootloader
2025-07-03 Too tired to finish .routing... @Meddy can you finish when I'm sleeping? Thanks :)
2025-07-03 still some drc, but teensy routing is done
2025-07-04 i fixed the stuff I could I have no clue what the new drc errors are
2025-07-04 a few small changes to make cyao happy!
2025-07-04 forgot to click b ;)
2025-07-06 there is only like 6 real traces left + power
2025-07-07 one more trace besides for power...
2025-07-07 Everything is wired besides for power and a few gnd stuff
2025-07-07 some drc fixes
2025-07-08 status light
2025-07-16 umm, routing stuff (lets make it clean this time for cyao :))
2025-07-18 Meddy, the PCB is ready for you. The proper RF is setup too on the PCB
2025-07-20 js added led
2025-07-20 simple wires
2025-07-20 ADD THIS TO .GITIGNORE!!!
2025-07-20 idk, started working on the gs schematic
2025-07-20 more rf routing
2025-07-20 thingy for programming
2025-07-20 schematic should be done for gs
2025-07-20 schematic fixes (3.3V and stuff) + started pcb
2025-07-20 more pcb stuff's
2025-07-20 lots of RF stuff done!
2025-07-20 60% of the routing is done
2025-07-20 I think the PCB is done for the ground station
2025-07-20 forgot D+ and D-... I don't want to wire it :(
2025-07-20 Data wires are routed
2025-07-21 added gs cad
2025-07-27 schematic stuff
2025-07-27 finished power stuff
2025-07-27 BE GONEf
2025-07-28 wiirng
2025-08-06 i forgot what i did
2025-08-11 push before i redo entire layout so i can revert
2025-08-13 started newest layout + wiring
2025-08-13 periodic commit
2025-08-14 im getting touched i touch you next
2025-08-14 random push
2025-08-14 taking a break
2025-08-16 daily commit
2025-08-18 extra push i forgot what i did
2025-08-18 save push not done
2025-08-19 power + usbc
2025-08-19 repour +saves
2025-08-19 power fixes
2025-08-19 refilled
2025-08-19 cleaned
2025-08-19 chips yummy
2025-08-19 more wiring fuck this
2025-08-20 finished basics, proof check time
2025-08-20 deleted random files
2025-08-21 more wiring kms
2025-08-22 wiring fml
2025-08-22 i did stuffs
2025-08-22 scooter please wire the stuff thats off the board to the side
2025-08-25 routed GPS for H1
2025-08-28 data lines fix :(
2025-08-28 wiring we can finish in lit 1-2 days max
2025-08-29 added BGM220SC12WGA2R
2025-08-29 force push :'/
2025-08-29 fixes
2025-08-29 more stuff
2025-08-29 more bl routing
2025-08-29 now you can continue
2025-08-31 gotta get those daily commits in
2025-08-31 work and updated from schematic
2025-08-31 review please before power rails
2025-08-31 did a lot of wiring stuffs
2025-08-31 added buzzer footprint
2025-09-01 push
2025-09-02 DONE DONE FUCKING DONE
2025-09-02 FUCK THIS SHIT EXTRA COMMIT BUT IM DONE
    FUCK I FORGOT LEDS AND LOGO AND SWD PINS
2025-09-02 fuck i thought i was done
    :( fml
2025-09-03 giveing a value to the mistery crystal
2025-09-03 more
2025-09-03 Update README.md
    fixng usrname
2025-09-05 FUCK YES 99.99999% DONE
    @scooterthedev CAN U FINISH WIRING LAST LED?
    + CYAO AND MAX CHECK PLEASE
2025-09-05 ima cum if we finish this week
2025-09-05 i think ima start pushing for fun commit messages
2025-09-05 i need worse commit messages
2025-09-06 doneeee fuck yeah fuck ts bih
2025-09-07 shortening
2025-09-08 good morning
2025-09-11 some cleanup
2025-09-12 there are problems that need to be fixed before being ordered
2025-09-12 woops, forgot to save lol
2025-09-15 fixed all drc. everything else is bs
2025-09-16 fk this i hate it im hungry
2025-09-16 everything everything :) wait no i still havent added the secondary rotary encoder dont push
2025-09-16 a lotta bug fixes in the PCB!
2025-09-17 lowky got no clue
2025-09-17 idt theres too much that can be improved in terms of wiring efficiency
2025-09-17 max please review before ordering
2025-09-17 swap spi lines on tmcu
2025-09-17 note: referenced to vddana
2025-09-18 swapping swd on nmcu
2025-09-18 samds look good to me
2025-09-19 if this breaks stuff womp womp
2025-09-19 bluetooth, gps, gyro reviewed - doing pressure tmrw
2025-09-19 oops
2025-09-19 only worked on the schematic, so the PCB is fine. Fixed a few small things- max, the baro looks right too
2025-09-19 imoved stuffs
2025-09-19 updated from schematic
2025-09-19 move some stuff aorund
2025-09-21 add footprints
2025-09-23 make pcb bettererer
2025-09-23 went through drc
2025-09-24 someone fix the 30deg cap
2025-09-25 save spot push not done
2025-09-25 mounting holes + wiring
2025-09-25 good drc
2025-09-25 holes
2025-09-25 done?
2025-09-26 finnnnal!
2025-09-26 mistake yay!
2025-10-24 fixed micro sd card direction and prod files
2025-10-26 fixed crystal
2025-10-26 done done
2025-10-26 switched back to 12pF for the 2 caps
2025-10-26 micro sd card was too slow. part would have went over :(
